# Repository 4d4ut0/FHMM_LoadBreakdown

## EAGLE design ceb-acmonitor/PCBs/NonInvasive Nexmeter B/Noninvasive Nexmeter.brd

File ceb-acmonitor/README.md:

# CEB

Desenvolvimento de Sistema Integrado para Avaliação de Resultados Energéticos em Projetos do Programa de Eficiência Energética da ANEEL

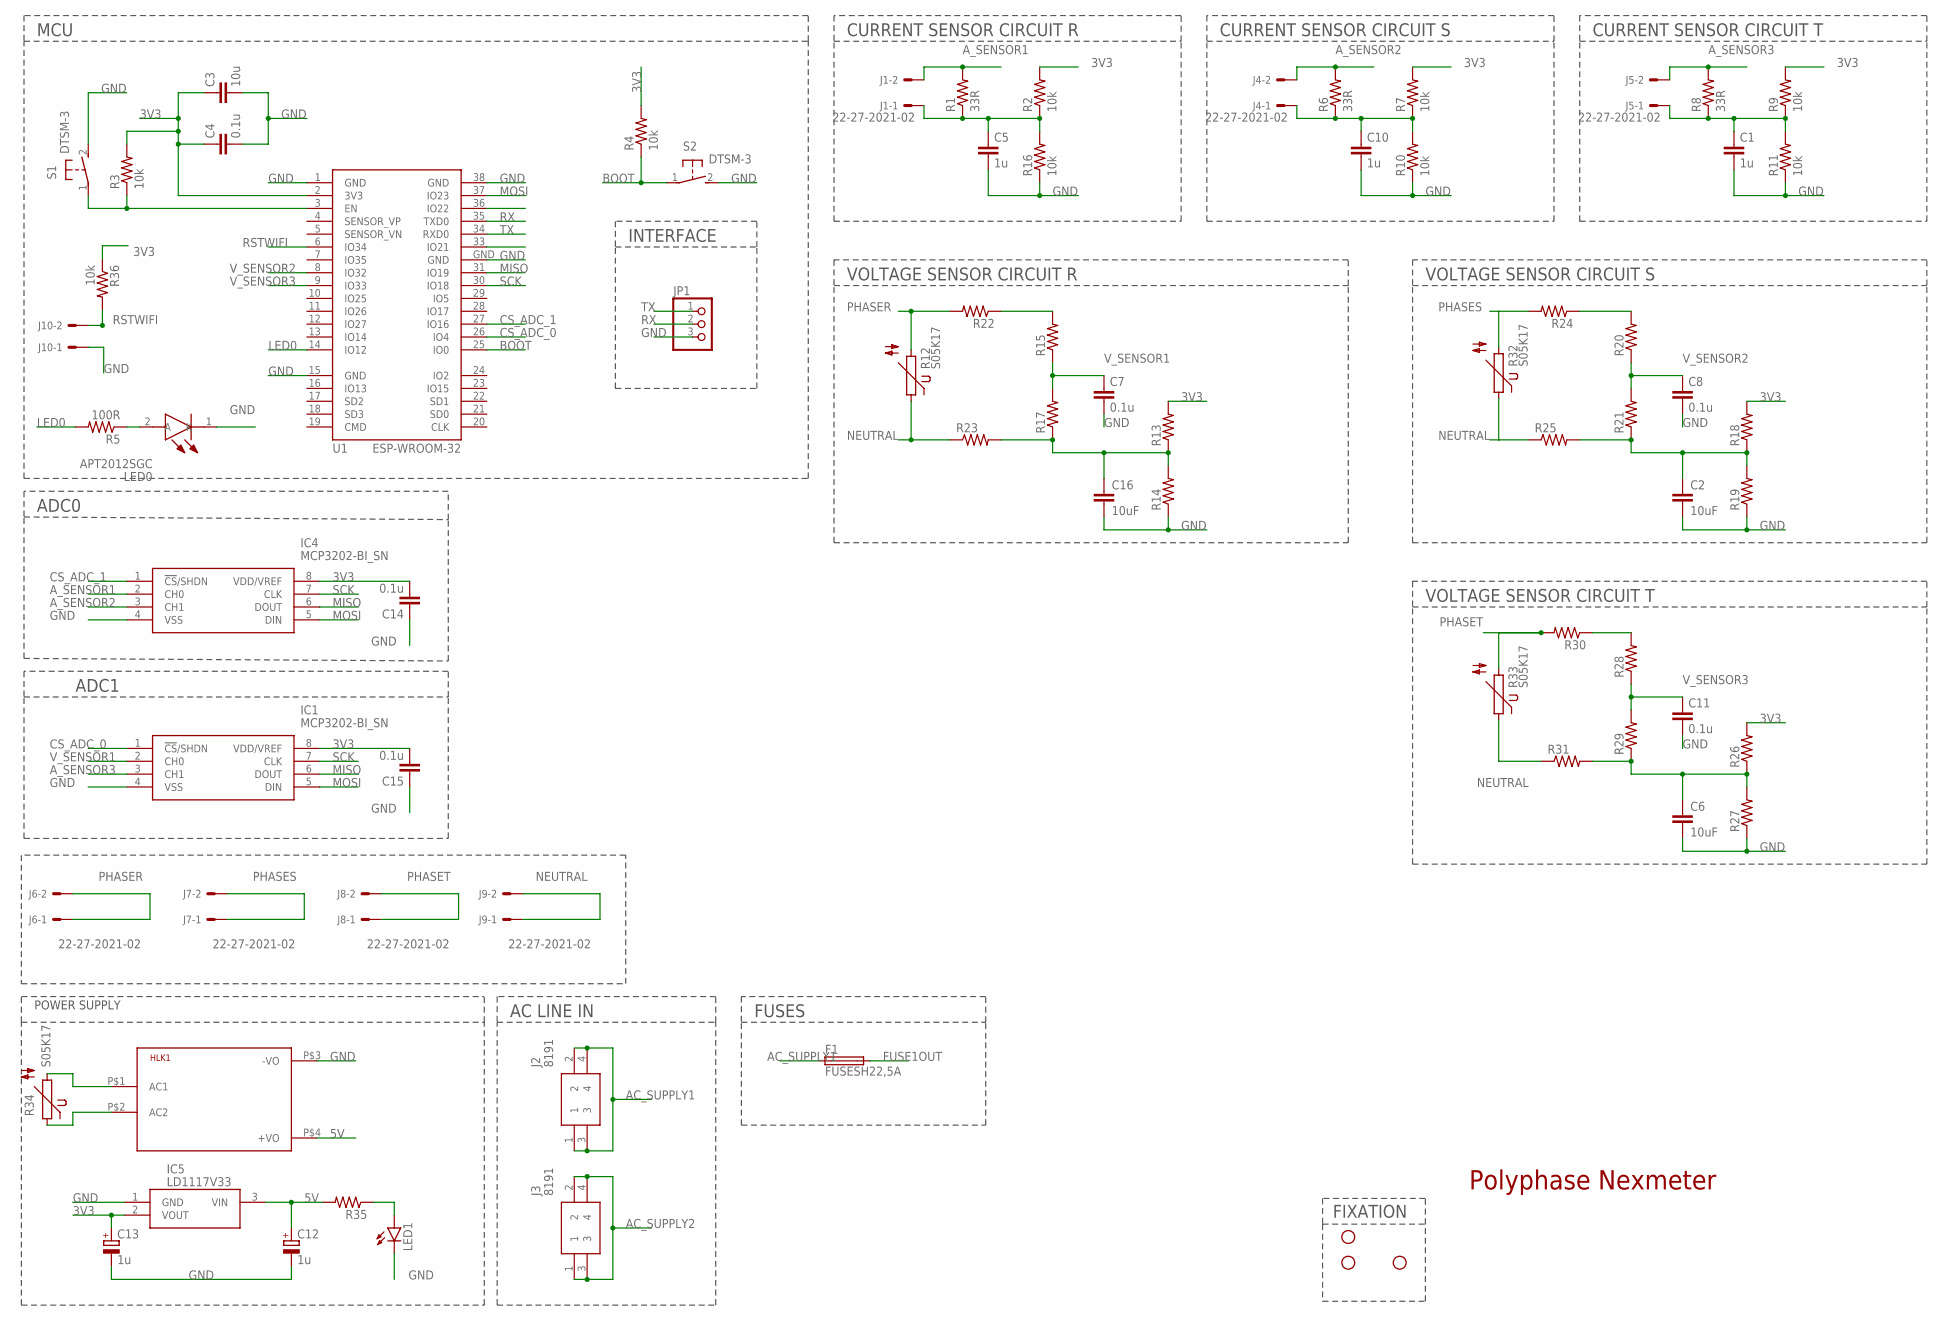
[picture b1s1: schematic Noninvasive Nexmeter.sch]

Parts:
C1, C5, C10: 1u; C0805
C2, C6, C16: 10uF; RCL_C0805
C3: 10u; C0805
C4, C7, C8, C11, C14, C15: 0.1u; C0805
C12, C13: 1u; E1,8-4
F1: FUSESH22,5A; SH22,5A
HLK1: HLK-PM013W; HLK-PM01
IC1, IC4: MCP3202-BI_SN; SOIC127P600X175-8N
IC5: LD1117V33; TO270P460X1020X2008-3P
J1, J4, J5, J6, J7, J8, J9, J10: 22-27-2021-02; 6410-02
J2, J3: 8191
JP1: PINHD-1X3; 1X03
LED0: APT2012SGC; LEDC2012X85N
LED1: LED5MM
R1, R6, R8: 33R; R0805
R2, R3, R4, R7, R9, R10, R11, R16, R36: 10k; R0805
R5: 100R; R0805
R12, R32, R33, R34: S05K17
R13, R14, R15, R17, R18, R19, R20, R21, R22, R23, R24, R25, R26, R27, R28, R29, R30, R31: 0805
R35: AXIAL-0.3
S1, S2: DTSM-3
STANDOFF1, STANDOFF2, STANDOFF4: STAND-OFF
U1: ESP-WROOM-32

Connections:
3V3: C3.1, C4.1, C13.+, C14.2, C15.2, IC1.8 (VDD/VREF), IC4.8 (VDD/VREF), IC5.2 (VOUT), R2.2, R3.2, R4.2, R7.2, R9.2, R13.2, R18.2, R26.2, R36.1, U1.2 (3V3)
5V: C12.+, HLK1.P$4 (+VO), IC5.3 (VIN), R35.P$2 (2)
AC_SUPPLY1: F1.1, J2.1, J2.2, J2.3, J2.4
AC_SUPPLY2: HLK1.P$2 (AC2), J3.1, J3.2, J3.3, J3.4, R34.1
A_SENSOR1: IC4.2 (CH0), J1.2, R1.2
A_SENSOR2: IC4.3 (CH1), J4.2, R6.2
A_SENSOR3: IC1.3 (CH1), J5.2, R8.2
BOOT: R4.1, S2.1, U1.25 (IO0)
CS_ADC_0: IC1.1 (!CS!/SHDN), U1.26 (IO4)
CS_ADC_1: IC4.1 (!CS!/SHDN), U1.27 (IO16)
FUSE1OUT: F1.2, HLK1.P$1 (AC1), R34.2
GND: C1.2, C2.2, C3.2, C4.2, C5.2, C6.2, C7.2, C8.2, C10.2, C11.2, C12.-, C13.-, C14.1, C15.1, C16.2, HLK1.P$3 (-VO), IC1.4 (VSS), IC4.4 (VSS), IC5.1 (GND), J10.1, JP1.3, LED0.1 (K), LED1.K (C), R10.1, R11.1, R14.1, R16.1, R19.1, R27.1, S1.2, S2.2, U1.1 (GND), U1.15 (GND), U1.38 (GND), U1.GND
LED0: R5.2, U1.14 (IO12)
MISO: IC1.6 (DOUT), IC4.6 (DOUT), U1.31 (IO19)
MOSI: IC1.5 (DIN), IC4.5 (DIN), U1.37 (IO23)
unnamed: R20.2, R24.1
unnamed: C1.1, J5.1, R8.1, R9.1, R11.2
unnamed: C2.1, R18.1, R19.2, R21.1, R25.2
unnamed: LED0.2 (A), R5.1
unnamed: R3.1, S1.1, U1.3 (EN)
unnamed: R28.2, R30.1
unnamed: R15.2, R22.1
unnamed: C10.1, J4.1, R6.1, R7.1, R10.2
unnamed: C16.1, R13.1, R14.2, R17.1, R23.2
unnamed: C6.1, R26.1, R27.2, R29.1, R31.2
unnamed: LED1.A, R35.P$1 (1)
unnamed: C5.1, J1.1, R1.1, R2.1, R16.2
NEUTRAL: J9.1, J9.2, R12.1, R23.1, R25.1, R31.1, R32.1, R33.1
PHASER: J6.1, J6.2, R12.2, R22.2
PHASES: J7.1, J7.2, R24.2, R32.2
PHASET: J8.1, J8.2, R30.2, R33.2
RSTWIFI: J10.2, R36.2, U1.6 (IO34)
RX: JP1.2, U1.35 (TXD0)
SCK: IC1.7 (CLK), IC4.7 (CLK), U1.30 (IO18)
TX: JP1.1, U1.34 (RXD0)
V_SENSOR1: C7.1, IC1.2 (CH0), R15.1, R17.2
V_SENSOR2: C8.1, R20.1, R21.2, U1.8 (IO32)
V_SENSOR3: C11.1, R28.1, R29.2, U1.9 (IO33)

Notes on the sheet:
Polyphase Nexmeter
FIXATION
POWER SUPPLY
MCU
INTERFACE
AC LINE IN
ADC0
FUSES
CURRENT SENSOR CIRCUIT R
CURRENT SENSOR CIRCUIT S
CURRENT SENSOR CIRCUIT T
VOLTAGE SENSOR CIRCUIT R
VOLTAGE SENSOR CIRCUIT S
VOLTAGE SENSOR CIRCUIT T
ADC1

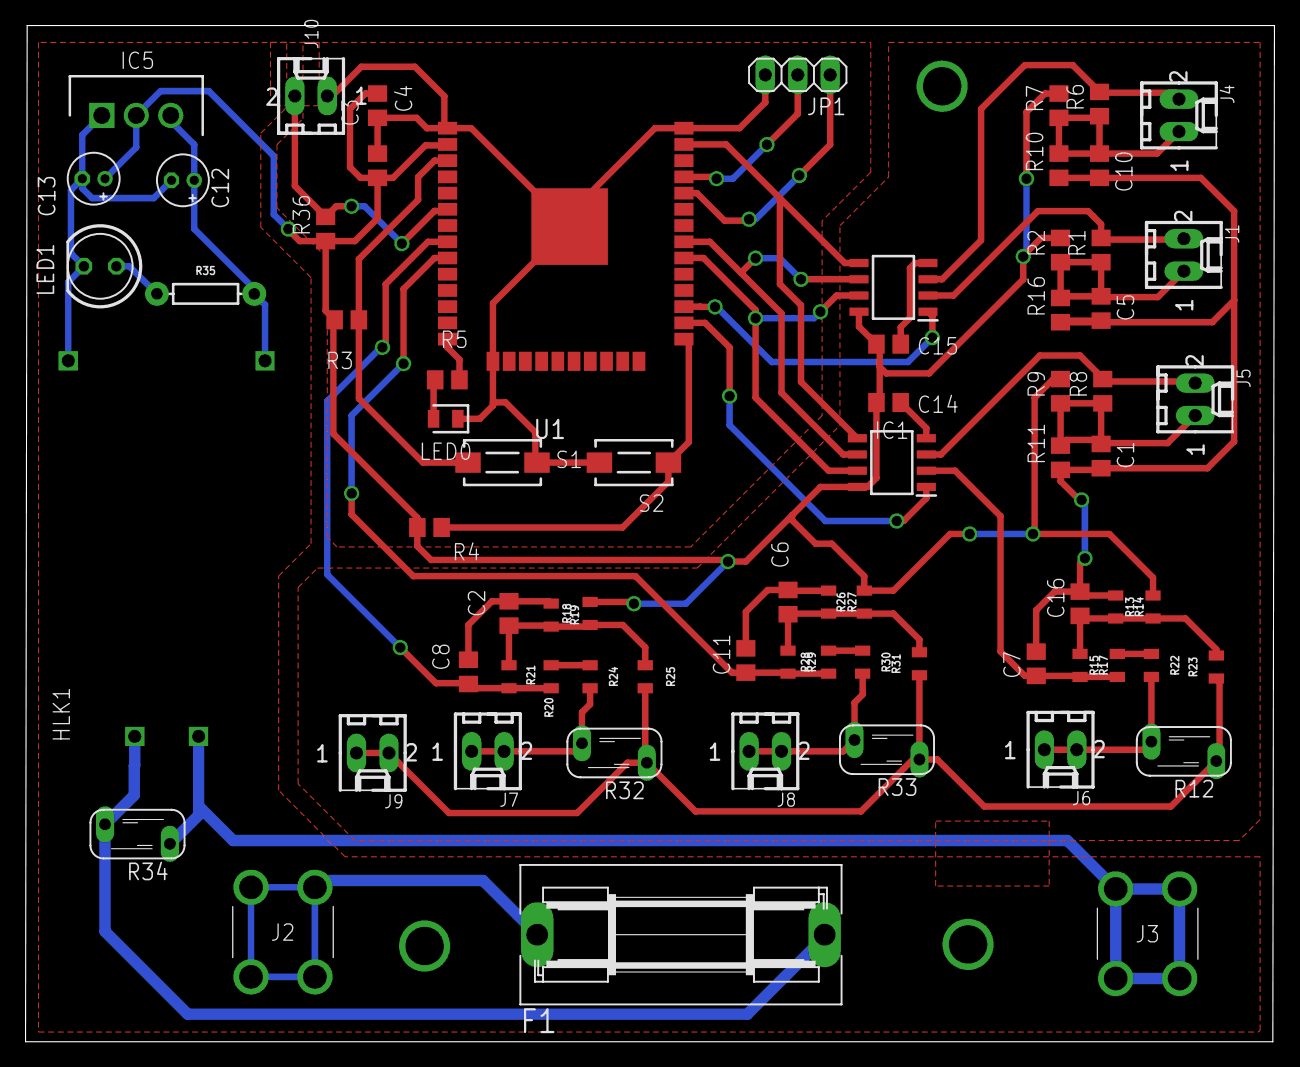
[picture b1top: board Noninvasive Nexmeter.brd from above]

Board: 2 copper layers, 97.8 x 79.6 mm, 75 parts (0 on the bottom side), 38 nets.

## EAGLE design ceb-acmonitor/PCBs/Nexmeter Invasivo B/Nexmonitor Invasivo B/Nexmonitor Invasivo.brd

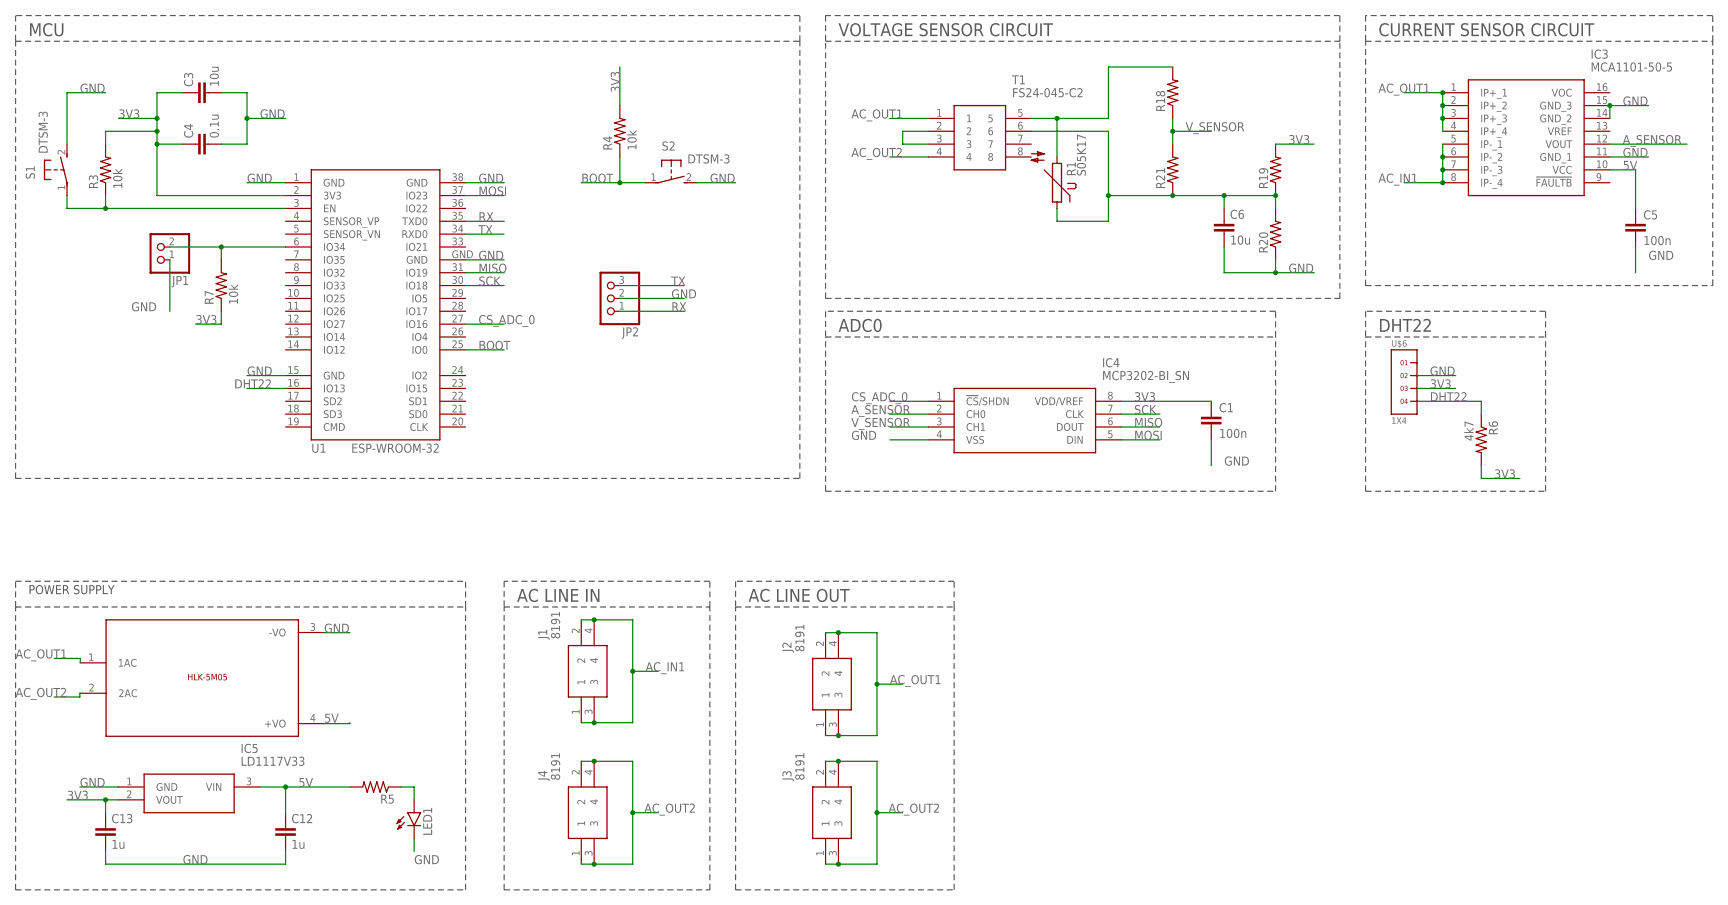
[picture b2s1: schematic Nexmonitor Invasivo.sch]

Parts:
C1, C5: 100n; C0805K
C3, C6: 10u; C0805
C4: 0.1u; C0805
C12, C13: 1u; C025-025X050
IC3: MCA1101-50-5; SOIC127P1031X264-16N
IC4: MCP3202-BI_SN; SOIC127P600X175-8N
IC5: LD1117V33; TO270P460X1020X2008-3P
J1, J2, J3, J4: 8191
JP1: PINHD-1X2; 1X02
JP2: PINHD-1X3; 1X03
LED1: LED5MM
R1: S05K17
R3, R4, R7: 10k; R0805
R5: 470; R0805
R6: 4k7; R0805
R18, R20: 470k; R0805
R19: 120k; R0805
R21: 33k; R0805
S1, S2: DTSM-3
T1: FS24-045-C2; FS24045C2
U1: ESP-WROOM-32
U$5: 5VDC/5W; HLK-5M05
U$6: 1X4

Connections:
3V3: C1.1, C3.1, C4.1, C13.1, IC4.8 (VDD/VREF), IC5.2 (VOUT), R3.2, R4.2, R6.2, R7.1, R19.2, U1.2 (3V3), U$6.3
5V: C5.1, C12.1, IC3.10 (VCC), IC5.3 (VIN), R5.2, U$5.4 (+VO)
AC_IN1: IC3.5 (IP-_1), IC3.6 (IP-_2), IC3.7 (IP-_3), IC3.8 (IP-_4), J1.1, J1.2, J1.3, J1.4
AC_OUT1: IC3.1 (IP+_1), IC3.2 (IP+_2), IC3.3 (IP+_3), IC3.4 (IP+_4), J2.1, J2.2, J2.3, J2.4, T1.1, U$5.1 (1AC)
AC_OUT2: J3.1, J3.2, J3.3, J3.4, J4.1, J4.2, J4.3, J4.4, T1.4, U$5.2 (2AC)
A_SENSOR: IC3.12 (VOUT), IC4.2 (CH0)
BOOT: R4.1, S2.1, U1.25 (IO0)
CS_ADC_0: IC4.1 (!CS!/SHDN), U1.27 (IO16)
DHT22: R6.1, U1.16 (IO13), U$6.4
GND: C1.2, C3.2, C4.2, C5.2, C6.2, C12.2, C13.2, IC3.11 (GND_1), IC3.14 (GND_2), IC3.15 (GND_3), IC4.4 (VSS), IC5.1 (GND), JP1.1, JP2.2, LED1.K (C), R20.1, S1.2, S2.2, U1.1 (GND), U1.15 (GND), U1.38 (GND), U1.GND, U$5.3 (-VO), U$6.2
MISO: IC4.6 (DOUT), U1.31 (IO19)
MOSI: IC4.5 (DIN), U1.37 (IO23)
unnamed: R1.2, R18.2, T1.5
unnamed: LED1.A, R5.1
unnamed: T1.2, T1.3
unnamed: JP1.2, R7.2, U1.6 (IO34)
unnamed: R3.1, S1.1, U1.3 (EN)
unnamed: C6.1, R1.1, R19.1, R20.2, R21.1, T1.6
RX: JP2.1, U1.35 (TXD0)
SCK: IC4.7 (CLK), U1.30 (IO18)
TX: JP2.3, U1.34 (RXD0)
V_SENSOR: IC4.3 (CH1), R18.1, R21.2

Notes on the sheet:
POWER SUPPLY
MCU
CURRENT SENSOR CIRCUIT
AC LINE IN
AC LINE OUT
DHT22
VOLTAGE SENSOR CIRCUIT
ADC0

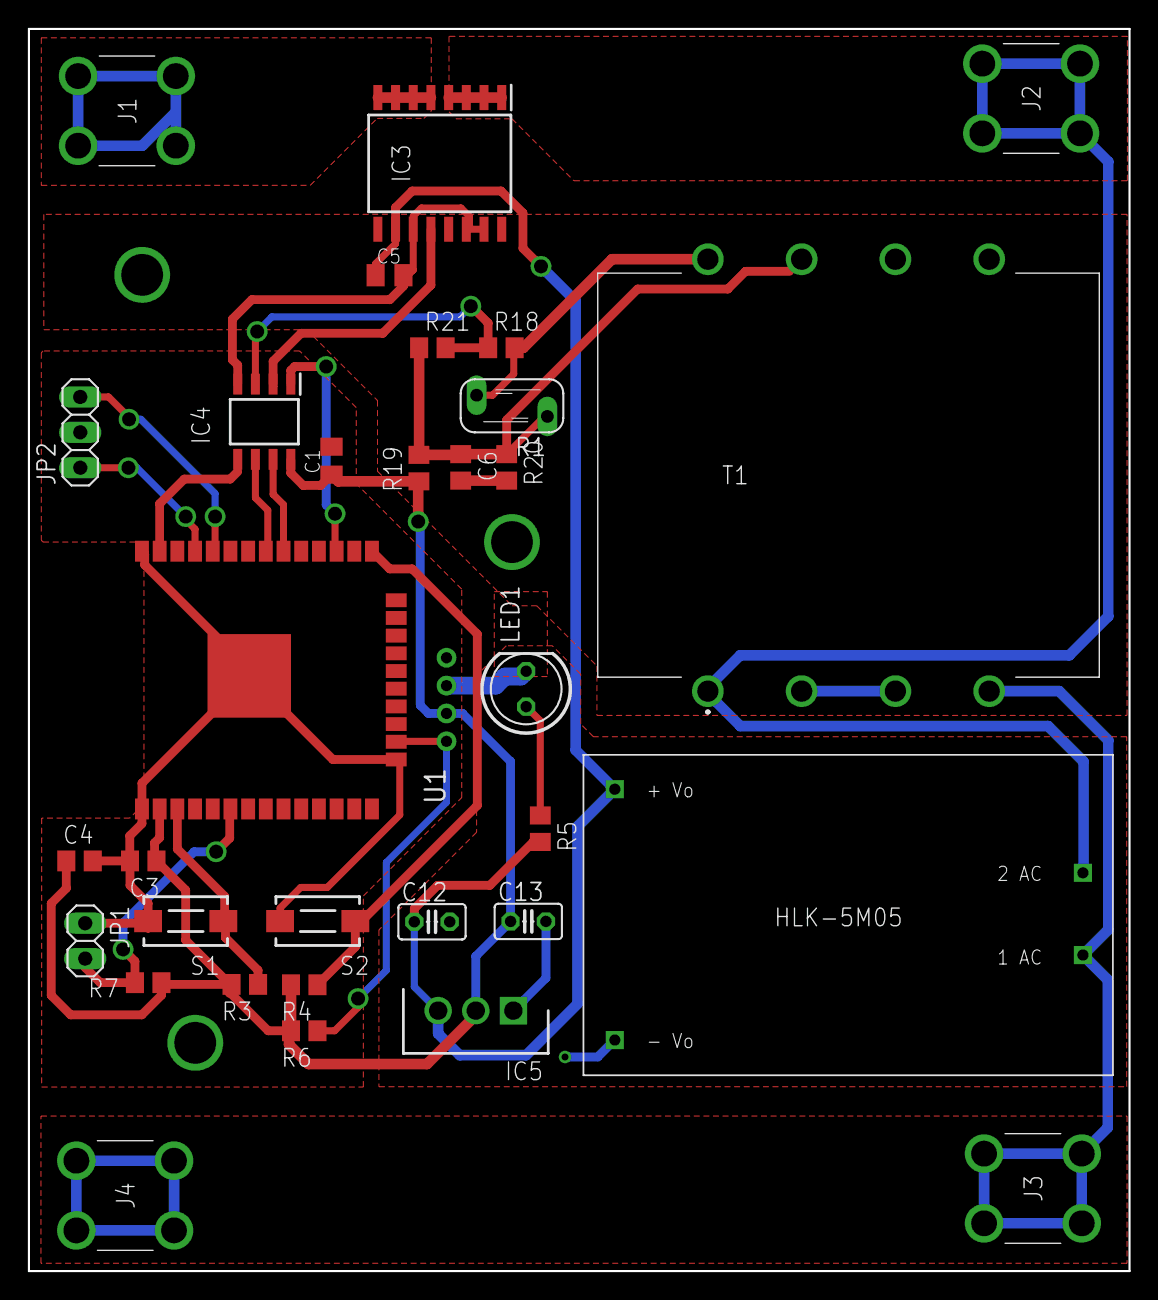
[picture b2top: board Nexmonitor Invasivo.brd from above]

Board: 2 copper layers, 79.0 x 89.2 mm, 33 parts (1 on the bottom side), 22 nets.

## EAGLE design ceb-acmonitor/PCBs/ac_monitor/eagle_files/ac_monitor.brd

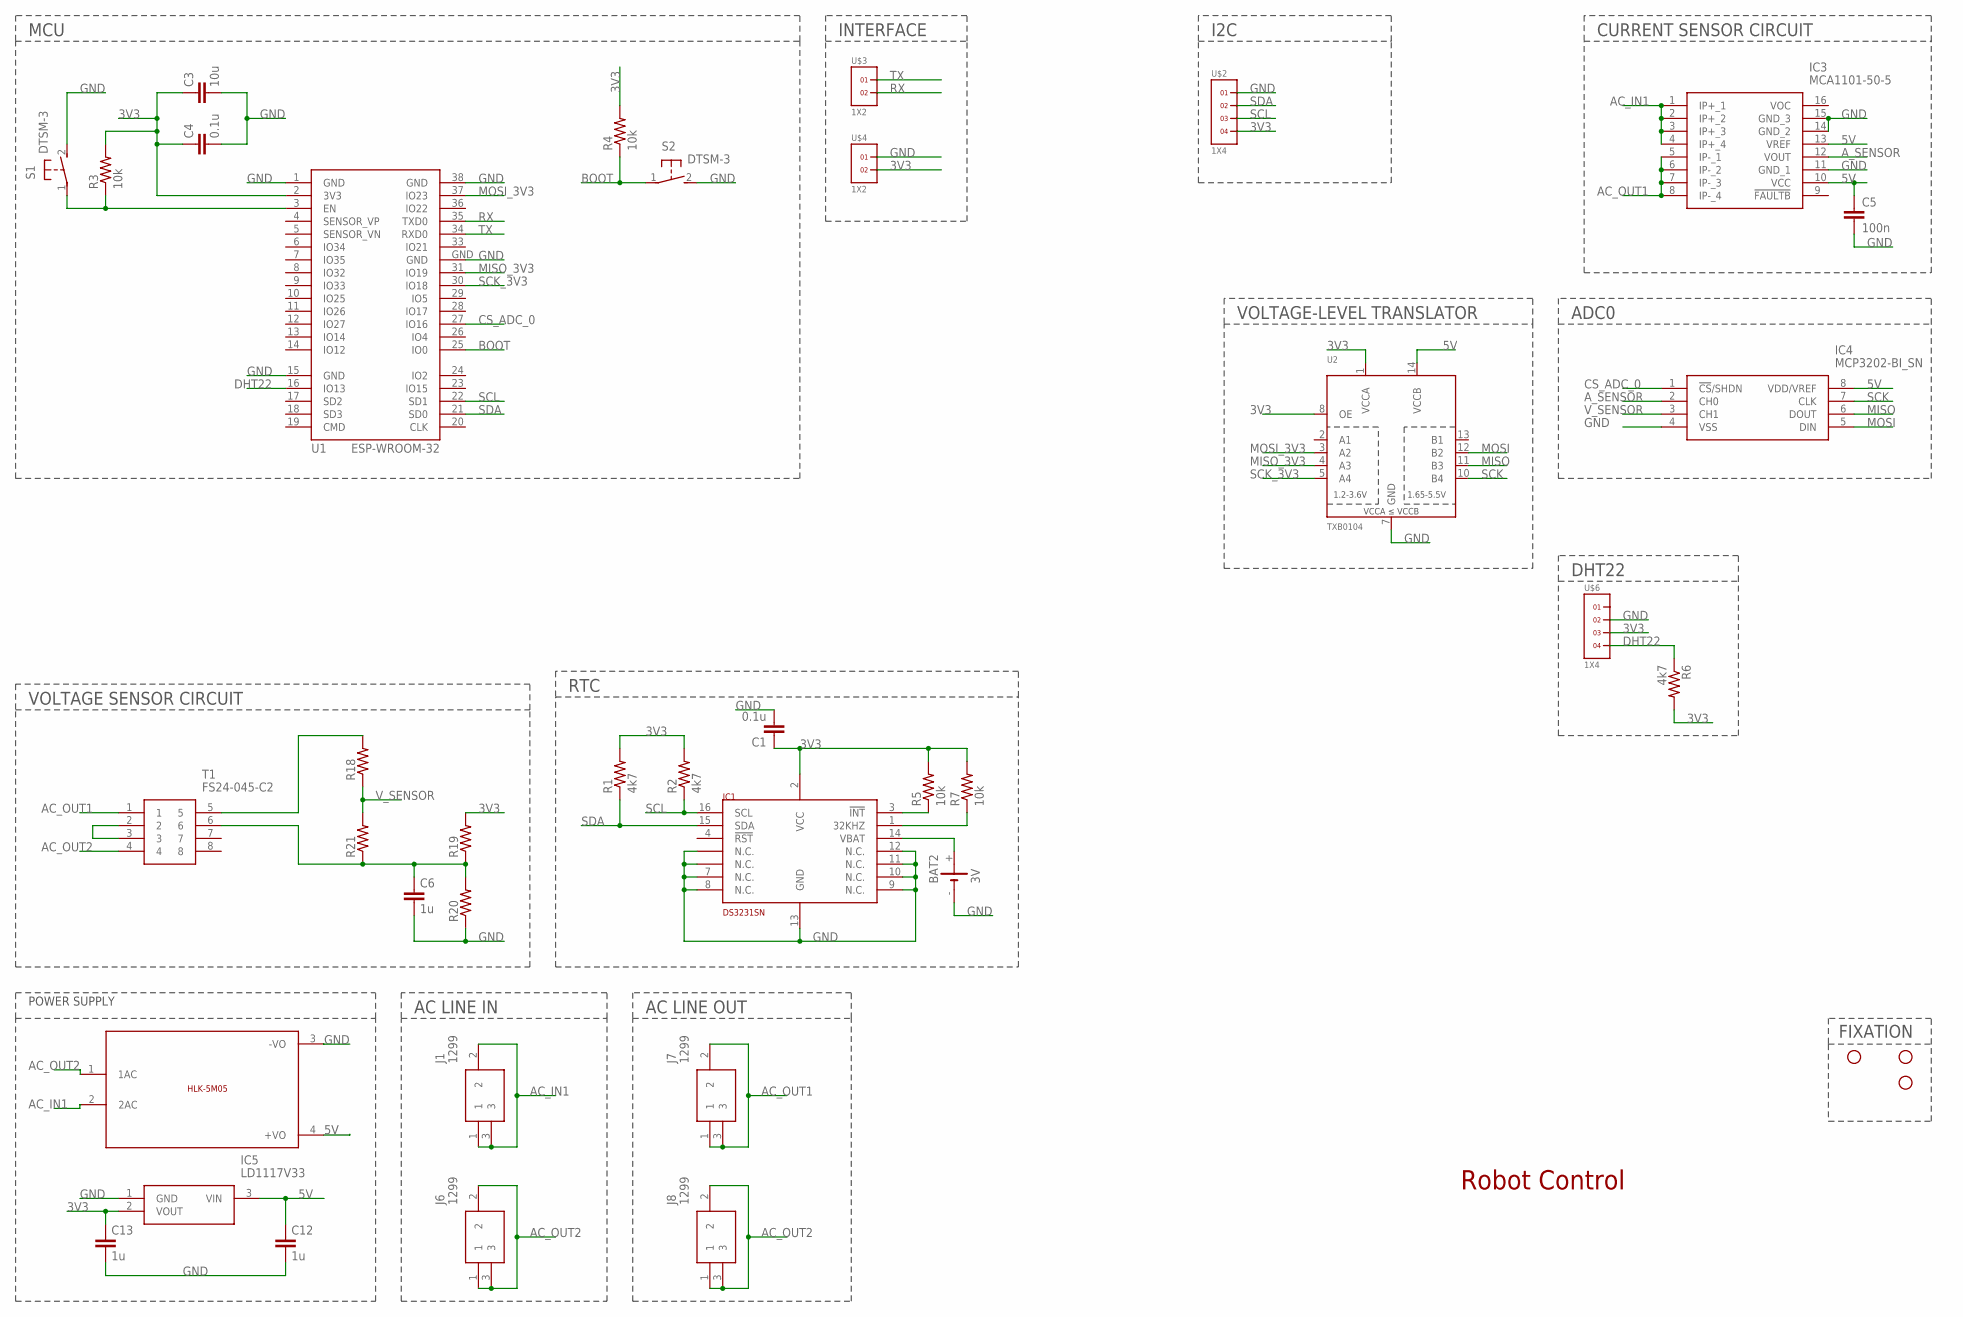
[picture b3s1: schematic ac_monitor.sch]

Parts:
BAT2: 3V; CH291-1220LF
C1: 0.1u; C0805K
C3: 10u; C0805
C4: 0.1u; C0805
C5: 100n; C0805K
C6: 1u; C0805
C12, C13: 1u; C025-025X050
IC1: DS3231SN; SO16W
IC3: MCA1101-50-5; SOIC127P1031X264-16N
IC4: MCP3202-BI_SN; SOIC127P600X175-8N
IC5: LD1117V33; TO270P460X1020X2008-3P
J1, J6, J7, J8: 1299
R1, R2, R6: 4k7; R0805
R3, R4, R5, R7: 10k; R0805
R18: 270k; R0805
R19: 120k; R0805
R20: 470k; R0805
R21: 33k; R0805
S1, S2: DTSM-3
STANDOFF2, STANDOFF3, STANDOFF4: STAND-OFF
T1: FS24-045-C2; FS24045C2
U1: ESP-WROOM-32
U2: TXB0104; TSSOP14
U$2, U$6: 1X4
U$3, U$4: 1X2
U$5: 5VDC/5W; HLK-5M05

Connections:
3V3: C1.1, C3.1, C4.1, C13.1, IC1.2 (VCC), IC5.2 (VOUT), R1.2, R2.2, R3.2, R4.2, R5.2, R6.2, R7.2, R19.2, U1.2 (3V3), U2.1 (VCCA), U2.8 (OE), U$2.4, U$4.2, U$6.3
5V: C5.1, C12.1, IC3.10 (VCC), IC3.13 (VREF), IC4.8 (VDD/VREF), IC5.3 (VIN), U2.14 (VCCB), U$5.4 (+VO)
AC_IN1: IC3.1 (IP+_1), IC3.2 (IP+_2), IC3.3 (IP+_3), IC3.4 (IP+_4), J1.1, J1.2, J1.3, U$5.2 (2AC)
AC_OUT1: IC3.5 (IP-_1), IC3.6 (IP-_2), IC3.7 (IP-_3), IC3.8 (IP-_4), J7.1, J7.2, J7.3, T1.1
AC_OUT2: J6.1, J6.2, J6.3, J8.1, J8.2, J8.3, T1.4, U$5.1 (1AC)
A_SENSOR: IC3.12 (VOUT), IC4.2 (CH0)
BOOT: R4.1, S2.1, U1.25 (IO0)
CS_ADC_0: IC4.1 (!CS!/SHDN), U1.27 (IO16)
DHT22: R6.1, U1.16 (IO13), U$6.4
GND: BAT2.-, C1.2, C3.2, C4.2, C5.2, C6.2, C12.2, C13.2, IC1.5 (N.C.), IC1.6 (N.C.), IC1.7 (N.C.), IC1.8 (N.C.), IC1.9 (N.C.), IC1.10 (N.C.), IC1.11 (N.C.), IC1.12 (N.C.), IC1.13 (GND), IC3.11 (GND_1), IC3.14 (GND_2), IC3.15 (GND_3), IC4.4 (VSS), IC5.1 (GND), R20.1, S1.2, S2.2, U1.1 (GND), U1.15 (GND), U1.38 (GND), U1.GND, U2.7 (GND), U$2.1, U$4.1, U$5.3 (-VO), U$6.2
MISO: IC4.6 (DOUT), U2.11 (B3)
MISO_3V3: U1.31 (IO19), U2.4 (A3)
MOSI: IC4.5 (DIN), U2.12 (B2)
MOSI_3V3: U1.37 (IO23), U2.3 (A2)
unnamed: R18.2, T1.5
unnamed: IC1.3 (!INT), R5.1
unnamed: T1.2, T1.3
unnamed: IC1.1 (32KHZ), R7.1
unnamed: R3.1, S1.1, U1.3 (EN)
unnamed: C6.1, R19.1, R20.2, R21.1, T1.6
unnamed: BAT2.+, IC1.14 (VBAT)
RX: U1.35 (TXD0), U$3.2
SCK: IC4.7 (CLK), U2.10 (B4)
SCK_3V3: U1.30 (IO18), U2.5 (A4)
SCL: IC1.16 (SCL), R2.1, U1.22 (SD1), U$2.3
SDA: IC1.15 (SDA), R1.1, U1.21 (SD0), U$2.2
TX: U1.34 (RXD0), U$3.1
V_SENSOR: IC4.3 (CH1), R18.1, R21.2

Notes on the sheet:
Robot Control
FIXATION
POWER SUPPLY
MCU
CURRENT SENSOR CIRCUIT
AC LINE IN
AC LINE OUT
DHT22
I2C
VOLTAGE SENSOR CIRCUIT
ADC0
INTERFACE
VOLTAGE-LEVEL TRANSLATOR
RTC

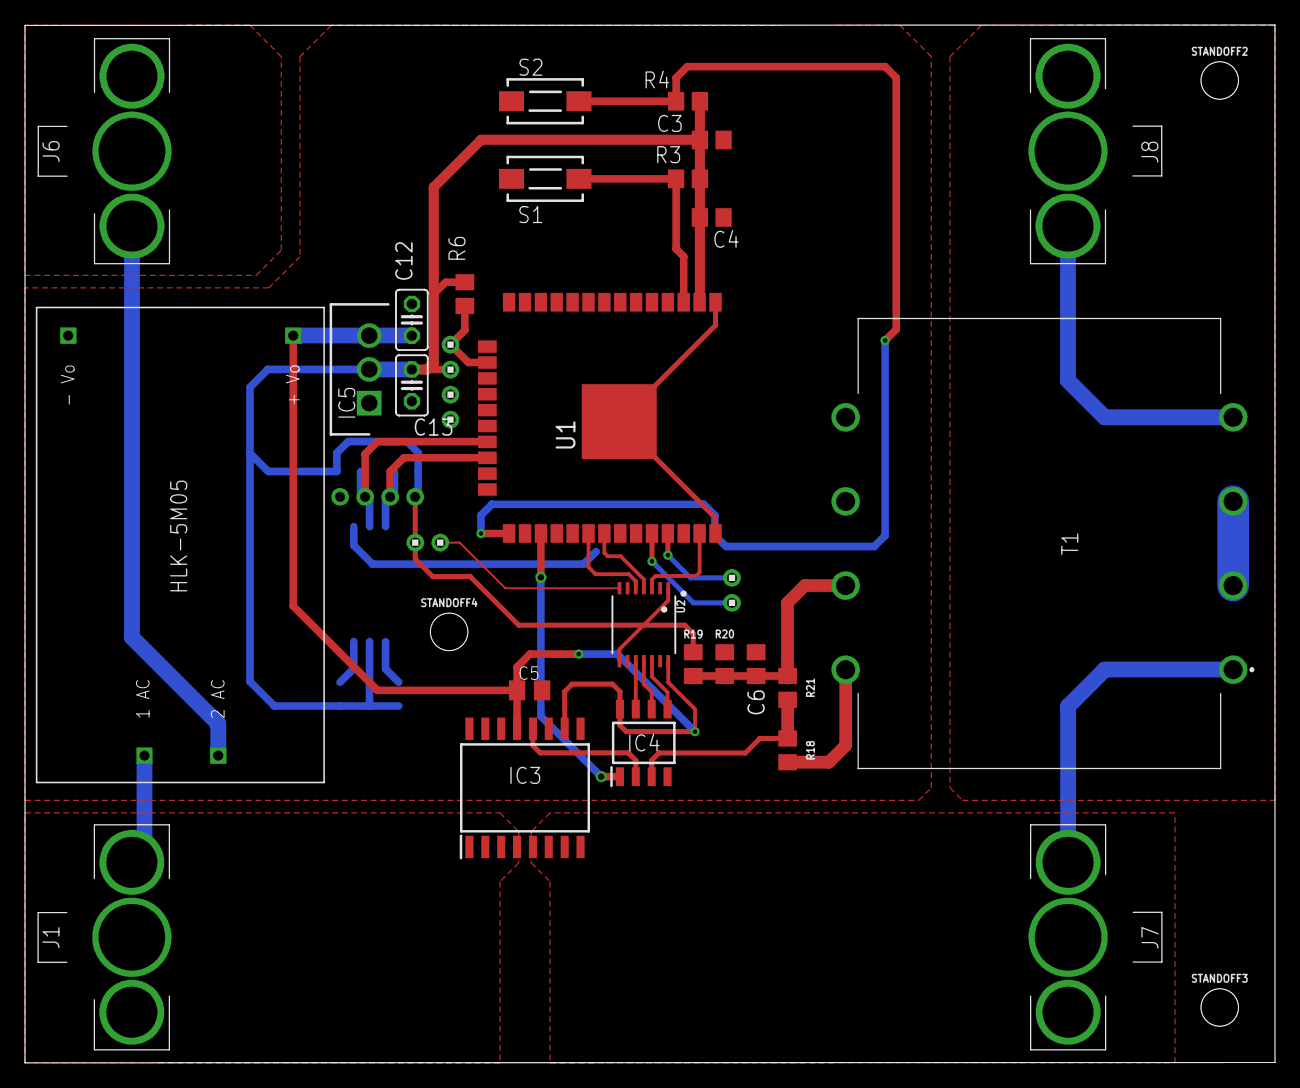
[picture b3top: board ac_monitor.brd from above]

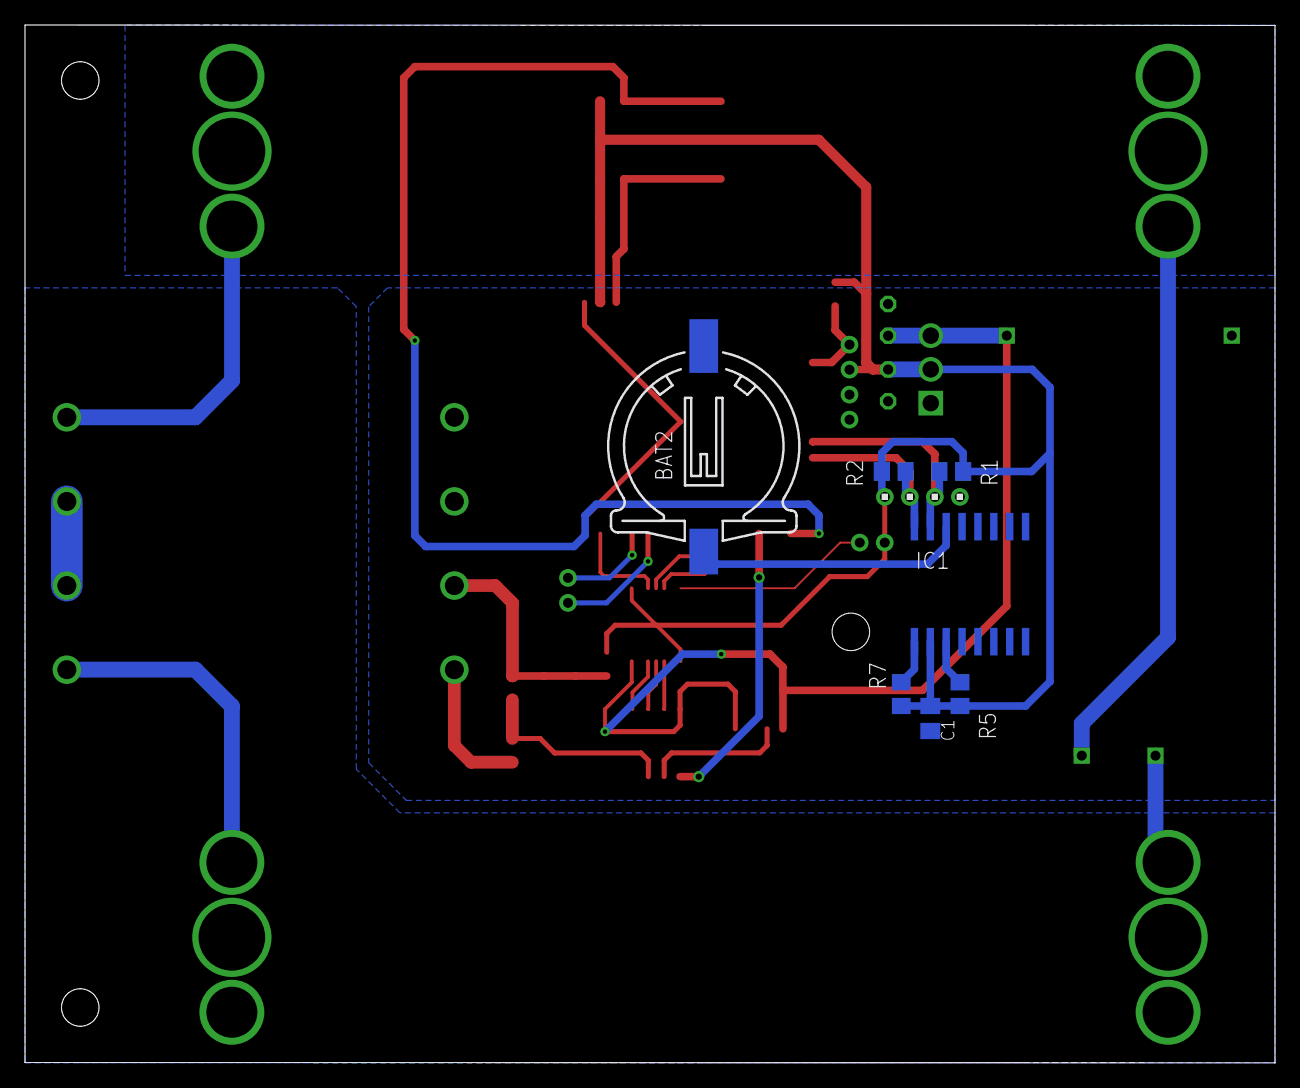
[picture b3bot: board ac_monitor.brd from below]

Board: 2 copper layers, 100.0 x 83.0 mm, 40 parts (8 on the bottom side), 28 nets.

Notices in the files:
parts and their libraries:
esp32: Creative Commons Attribution-ShareAlike 4.0 International
SparkFun-Resistors: Licensing: Creative Commons ShareAlike 4.0 International - https://creativecommons.org/licenses/by-sa/4.0
